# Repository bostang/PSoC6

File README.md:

# PSoC6
 Repository untuk program yang dijalankan pada PSoC6 (belajar dan hands-on project)

## Pranala Penting

[Hardware Abstraction Layer (HAL)](https://infineon.github.io/psoc6hal/html/index.html)

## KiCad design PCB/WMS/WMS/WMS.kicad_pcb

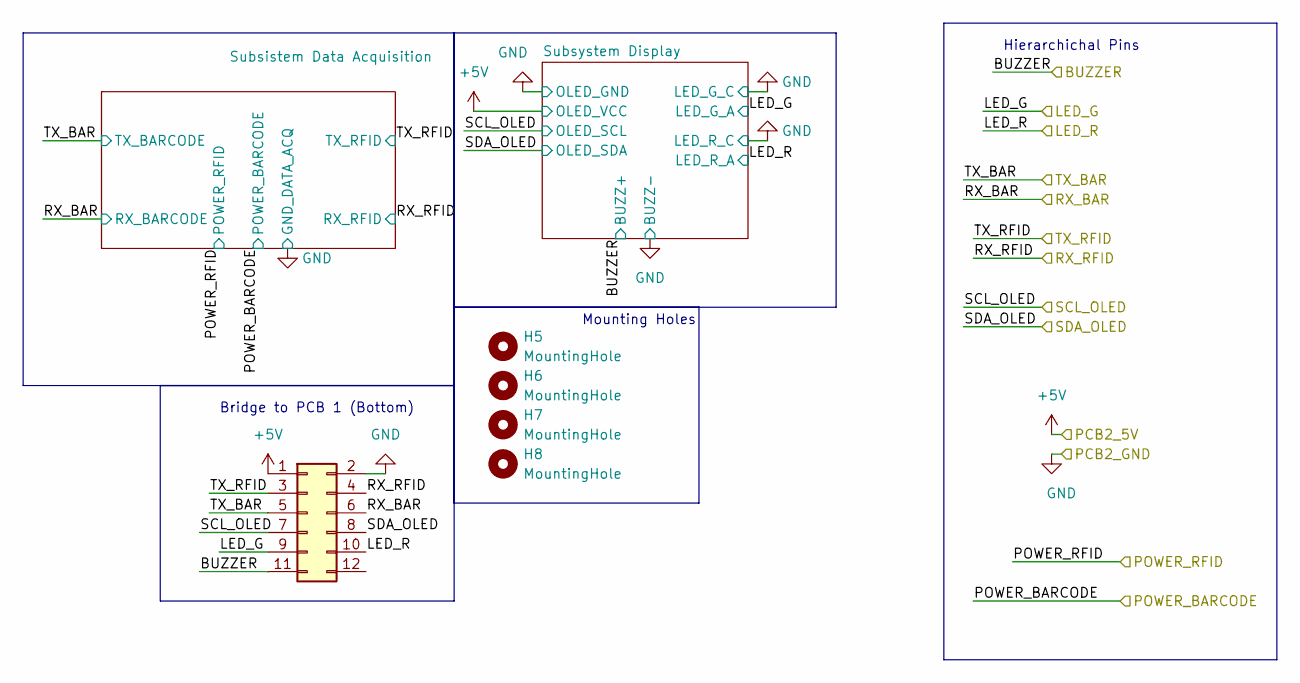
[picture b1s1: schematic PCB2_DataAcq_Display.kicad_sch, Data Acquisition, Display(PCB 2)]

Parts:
H5, H6, H7, H8: MountingHole; MountingHole_2.2mm_M2
J5: Conn_02x06_Odd_Even; JST_PHD_B12B-PHDSS_2x06_P2.00mm_Vertical

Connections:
+5V: J5.1; also elsewhere on the board
GND: J5.2; also elsewhere on the board
P6_0: J5.7; also elsewhere on the board
P6_1: J5.8; also elsewhere on the board
P9_0: J5.6; also elsewhere on the board
P9_1: J5.5; also elsewhere on the board
P9_2: J5.9; also elsewhere on the board
P9_4: J5.10; also elsewhere on the board
P12_0: J5.3; also elsewhere on the board
P12_1: J5.4; also elsewhere on the board
P12_3: J5.11; also elsewhere on the board

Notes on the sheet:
Mounting Holes
Bridge to PCB 1 (Bottom)
Hierarchichal Pins

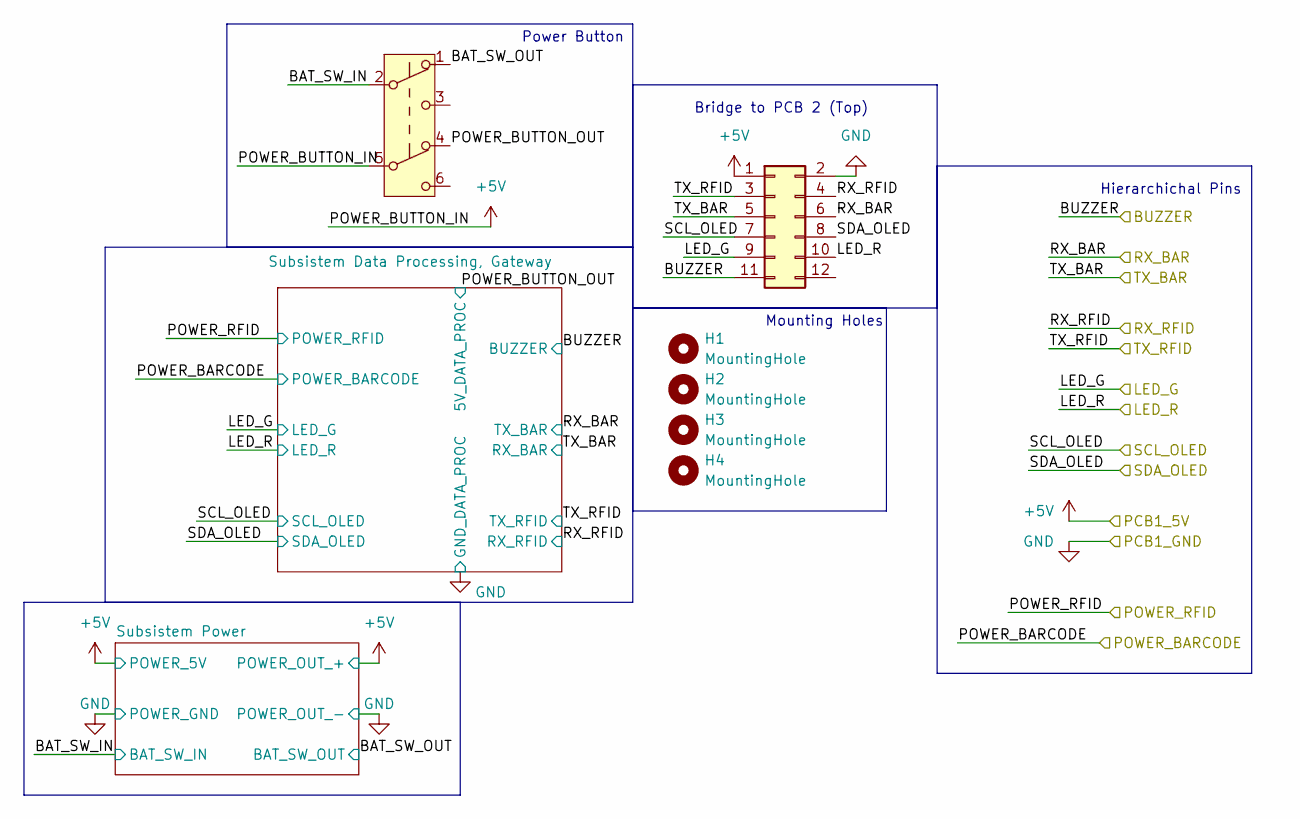
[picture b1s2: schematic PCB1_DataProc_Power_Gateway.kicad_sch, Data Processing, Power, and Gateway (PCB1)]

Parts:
H1, H2, H3, H4: MountingHole; MountingHole_2.2mm_M2
J4: Conn_02x06_Odd_Even; JST_PHD_B12B-PHDSS_2x06_P2.00mm_Vertical
SW2: SW_Push_DPDT; SW_E-Switch_EG2219_DPDT_Angled

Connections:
+5V: J4.1, SW2.5 (B); also elsewhere on the board
/PCB1 : Subsistem Data Processing, Gateway, Power/BAT_SW_IN: SW2.2 (B); also elsewhere on the board
/PCB1 : Subsistem Data Processing, Gateway, Power/BAT_SW_OUT: SW2.1 (A); also elsewhere on the board
/PCB1 : Subsistem Data Processing, Gateway, Power/POWER_BUTTON_OUT: SW2.4 (A); also elsewhere on the board
GND: J4.2; also elsewhere on the board
P6_0: J4.7; also elsewhere on the board
P6_1: J4.8; also elsewhere on the board
P9_0: J4.5; also elsewhere on the board
P9_1: J4.6; also elsewhere on the board
P9_2: J4.9; also elsewhere on the board
P9_4: J4.10; also elsewhere on the board
P12_0: J4.4; also elsewhere on the board
P12_1: J4.3; also elsewhere on the board
P12_3: J4.11; also elsewhere on the board

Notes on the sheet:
Hierarchichal Pins
Bridge to PCB 2 (Top)
Mounting Holes
Power Button

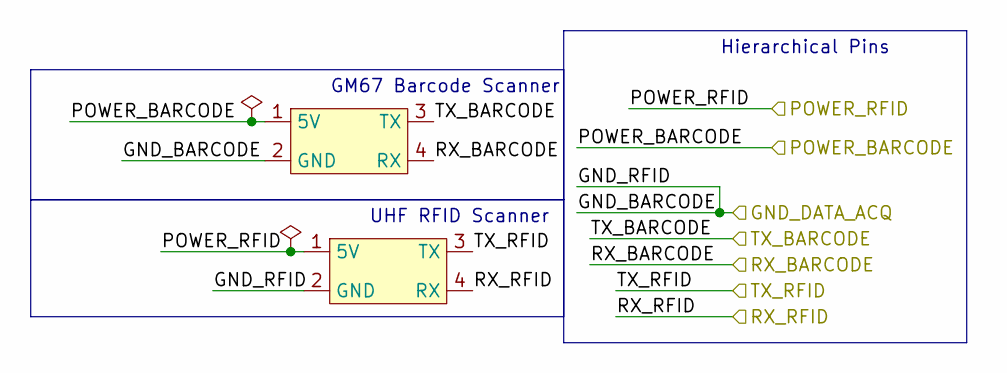
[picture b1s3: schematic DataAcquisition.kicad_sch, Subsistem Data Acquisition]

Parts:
U4, U5: GM67_Barcode_Scanner

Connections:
/PCB1 : Subsistem Data Processing, Gateway, Power/POWER_BARCODE: U4.1 (5V); also elsewhere on the board
/PCB1 : Subsistem Data Processing, Gateway, Power/POWER_RFID: U5.1 (5V); also elsewhere on the board
GND: U4.2 (GND), U5.2 (GND); also elsewhere on the board
P9_0: U4.4 (RX); also elsewhere on the board
P9_1: U4.3 (TX); also elsewhere on the board
P12_0: U5.3 (TX); also elsewhere on the board
P12_1: U5.4 (RX); also elsewhere on the board

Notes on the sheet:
UHF RFID Scanner
Hierarchical Pins
GM67 Barcode Scanner

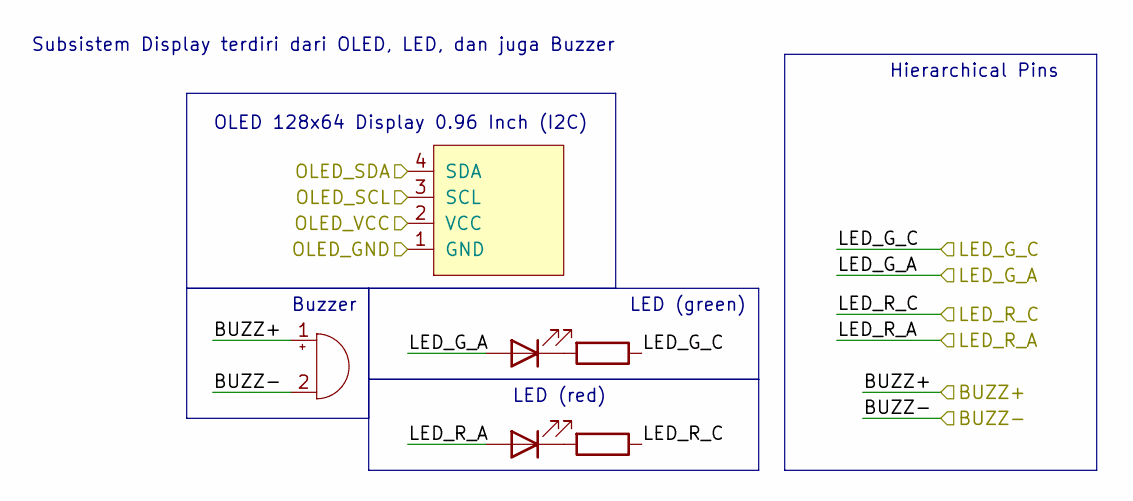
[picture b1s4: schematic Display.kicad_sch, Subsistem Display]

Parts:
BZ1: Buzzer; Buzzer_12x9.5RM7.6
Brd1: SSD1306; 128x64OLED
D1, D2: LED; LED_0805_2012Metric
R1, R2: R; R_0805_2012Metric

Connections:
+5V: Brd1.2 (VCC); also elsewhere on the board
GND: BZ1.2 (-), Brd1.1 (GND), R1.1, R2.1; also elsewhere on the board
unnamed: D1.1 (K), R1.2
unnamed: D2.1 (K), R2.2
P6_0: Brd1.3 (SCL); also elsewhere on the board
P6_1: Brd1.4 (SDA); also elsewhere on the board
P9_2: D1.2 (A); also elsewhere on the board
P9_4: D2.2 (A); also elsewhere on the board
P12_3: BZ1.1 (+); also elsewhere on the board

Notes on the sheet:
Subsistem Display terdiri dari OLED, LED, dan juga Buzzer
LED (red)
Buzzer
OLED 128x64 Display 0.96 Inch (I2C)
Hierarchical Pins
LED (green)

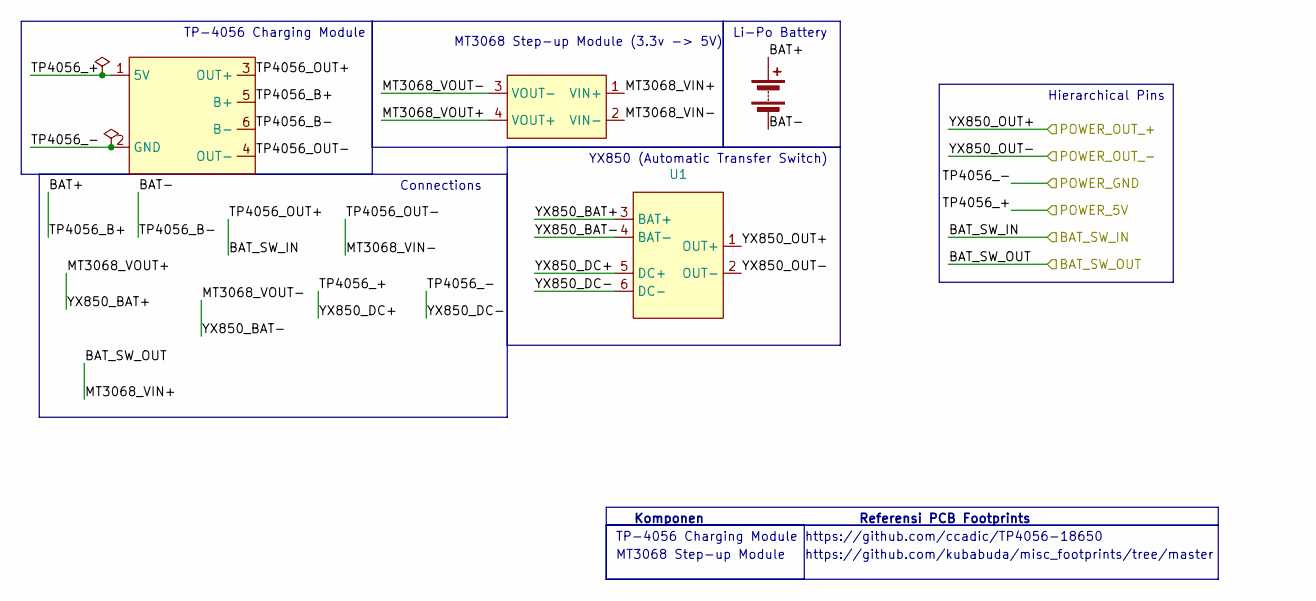
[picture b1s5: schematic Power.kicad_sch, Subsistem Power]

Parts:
BT1: Battery; JST_XH_B2B-XH-A_1x02_P2.50mm_Vertical
U1: YX850
U2: MT3608_module
U3: TP4056-18650

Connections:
+5V: U1.1 (OUT+), U1.5 (DC+), U3.1 (5V); also elsewhere on the board
/PCB1 : Subsistem Data Processing, Gateway, Power/BAT_SW_IN: U3.3 (OUT+); also elsewhere on the board
/PCB1 : Subsistem Data Processing, Gateway, Power/BAT_SW_OUT: U2.1 (VIN+); also elsewhere on the board
/PCB1 : Subsistem Data Processing, Gateway, Power/Subsistem Power/BAT+: BT1.1 (+), U3.5 (B+)
/PCB1 : Subsistem Data Processing, Gateway, Power/Subsistem Power/BAT-: BT1.2 (-), U3.6 (B-)
/PCB1 : Subsistem Data Processing, Gateway, Power/Subsistem Power/MT3068_VIN-: U2.2 (VIN-), U3.4 (OUT-)
/PCB1 : Subsistem Data Processing, Gateway, Power/Subsistem Power/MT3068_VOUT+: U1.3 (BAT+), U2.4 (VOUT+)
/PCB1 : Subsistem Data Processing, Gateway, Power/Subsistem Power/MT3068_VOUT-: U1.4 (BAT-), U2.3 (VOUT-)
GND: U1.2 (OUT-), U1.6 (DC-), U3.2 (GND); also elsewhere on the board

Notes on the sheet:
https://github.com/ccadic/TP4056-18650
https://github.com/kubabuda/misc_footprints/tree/master
TP-4056 Charging Module
Hierarchical Pins
Li-Po Battery
Komponen
MT3068 Step-up Module
YX850 (Automatic Transfer Switch)
Connections
Referensi PCB Footprints
MT3068 Step-up Module (3.3v -> 5V)

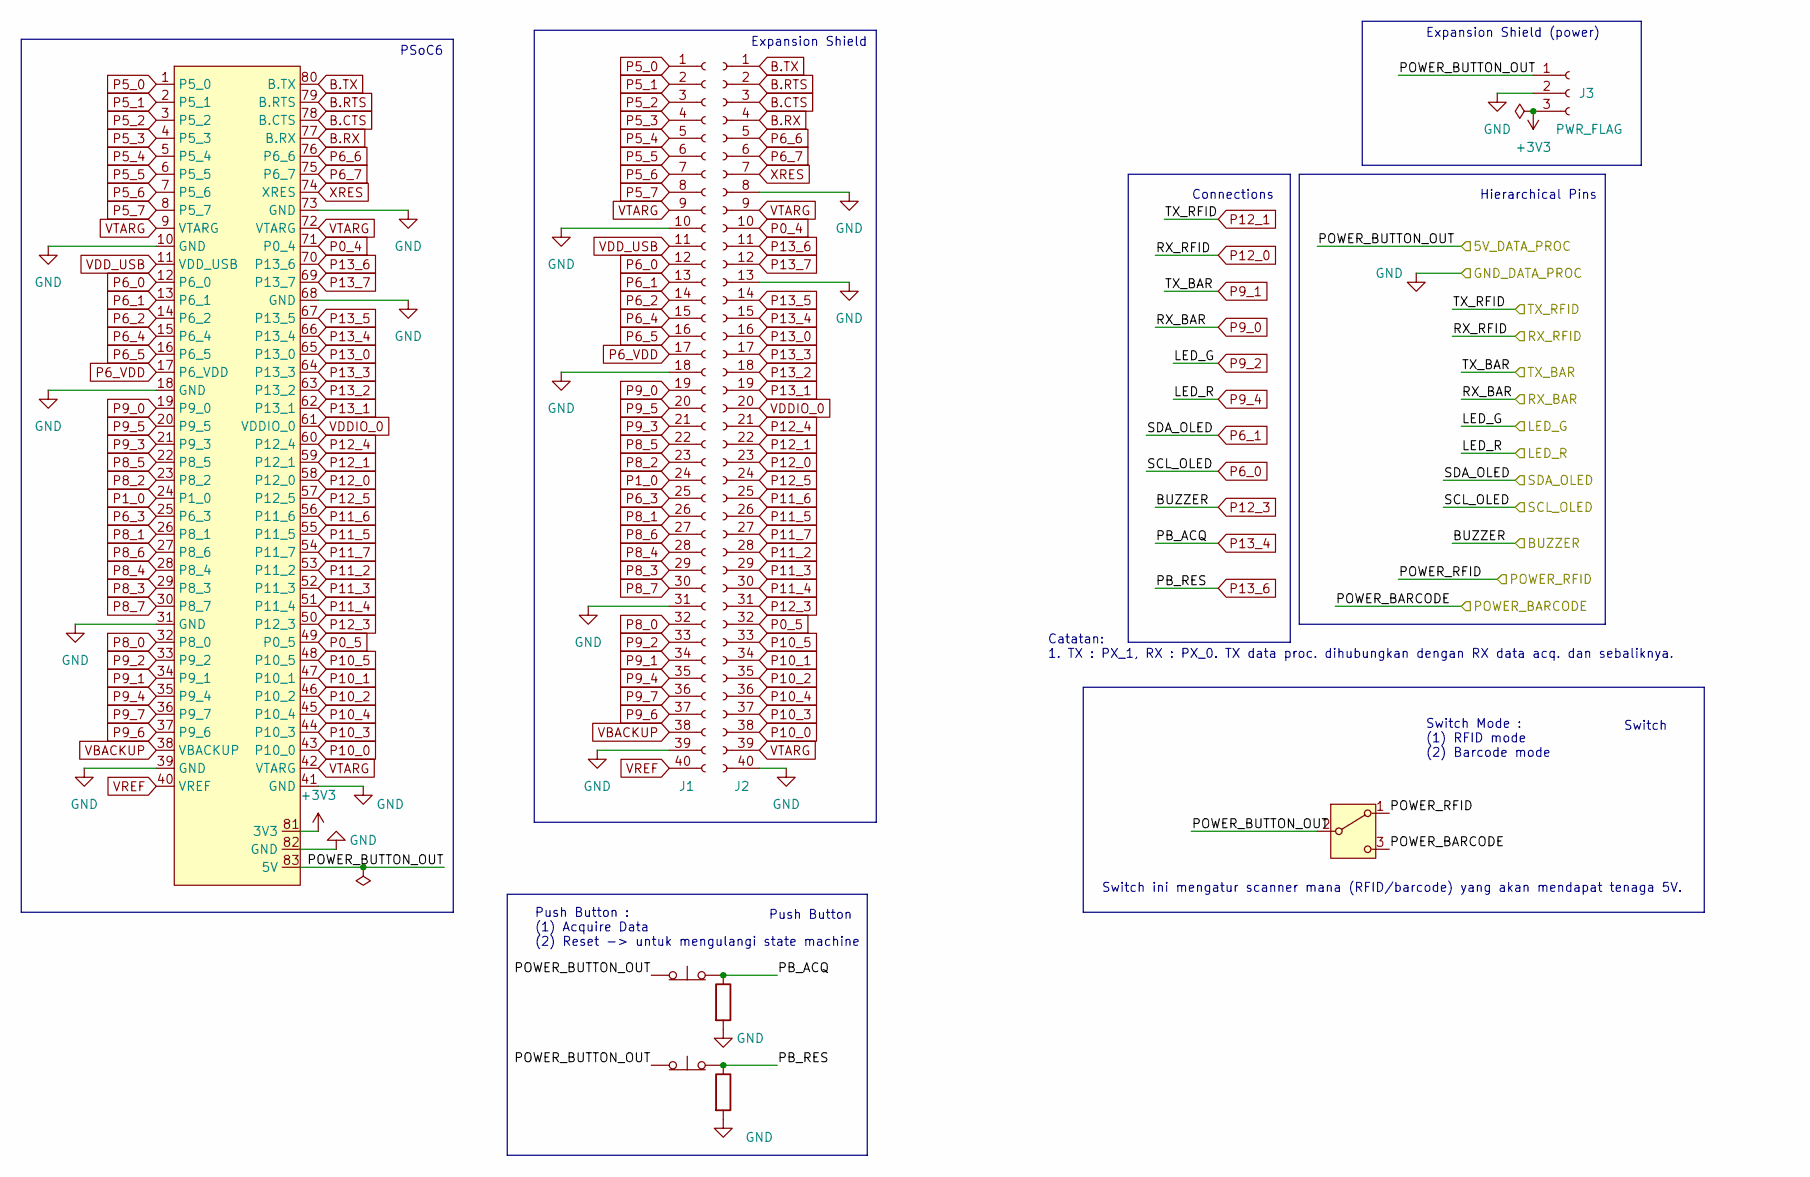
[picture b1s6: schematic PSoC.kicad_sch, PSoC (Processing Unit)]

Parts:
J1, J2: Conn_01x40_Socket; PinHeader_1x40_P2.54mm_Vertical
J3: Conn_01x03_Socket; PinHeader_1x03_P2.54mm_Vertical
R3, R4: R; R_0805_2012Metric
SW1, SW3: SW_Push_Open; SW_PUSH_6mm_H9.5mm
SW4: SW_SPDT; SW_E-Switch_EG1224_SPDT_Angled
U6: CY8CPROTO-062-4343W

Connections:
+3V3: J3.3, U6.81 (3V3)
/PCB1 : Subsistem Data Processing, Gateway, Power/POWER_BARCODE: SW4.3 (C); also elsewhere on the board
/PCB1 : Subsistem Data Processing, Gateway, Power/POWER_BUTTON_OUT: J3.1, SW1.1 (A), SW3.1 (A), SW4.2 (B), U6.83 (5V); also elsewhere on the board
/PCB1 : Subsistem Data Processing, Gateway, Power/POWER_RFID: SW4.1 (A); also elsewhere on the board
B.CTS: J2.3, U6.78 (B.CTS)
B.RTS: J2.2, U6.79 (B.RTS)
B.RX: J2.4, U6.77 (B.RX)
B.TX: J2.1, U6.80 (B.TX)
GND: J1.10, J1.18, J1.31, J1.39, J2.8, J2.13, J2.40, J3.2, R3.2, R4.2, U6.10 (GND), U6.18 (GND), U6.31 (GND), U6.39 (GND), U6.41 (GND), U6.68 (GND), U6.73 (GND), U6.82 (GND); also elsewhere on the board
P0_4: J2.10, U6.71 (P0_4)
P0_5: J2.32, U6.49 (P0_5)
P1_0: J1.24, U6.24 (P1_0)
P5_0: J1.1, U6.1 (P5_0)
P5_1: J1.2, U6.2 (P5_1)
P5_2: J1.3, U6.3 (P5_2)
P5_3: J1.4, U6.4 (P5_3)
P5_4: J1.5, U6.5 (P5_4)
P5_5: J1.6, U6.6 (P5_5)
P5_6: J1.7, U6.7 (P5_6)
P5_7: J1.8, U6.8 (P5_7)
P6_0: J1.12, U6.12 (P6_0); also elsewhere on the board
P6_1: J1.13, U6.13 (P6_1); also elsewhere on the board
P6_2: J1.14, U6.14 (P6_2)
P6_3: J1.25, U6.25 (P6_3)
P6_4: J1.15, U6.15 (P6_4)
P6_5: J1.16, U6.16 (P6_5)
P6_6: J2.5, U6.76 (P6_6)
P6_7: J2.6, U6.75 (P6_7)
P6_VDD: J1.17, U6.17 (P6_VDD)
P8_0: J1.32, U6.32 (P8_0)
P8_1: J1.26, U6.26 (P8_1)
P8_2: J1.23, U6.23 (P8_2)
P8_3: J1.29, U6.29 (P8_3)
P8_4: J1.28, U6.28 (P8_4)
P8_5: J1.22, U6.22 (P8_5)
P8_6: J1.27, U6.27 (P8_6)
P8_7: J1.30, U6.30 (P8_7)
P9_0: J1.19, U6.19 (P9_0); also elsewhere on the board
P9_1: J1.34, U6.34 (P9_1); also elsewhere on the board
P9_2: J1.33, U6.33 (P9_2); also elsewhere on the board
P9_3: J1.21, U6.21 (P9_3)
P9_4: J1.35, U6.35 (P9_4); also elsewhere on the board
P9_5: J1.20, U6.20 (P9_5)
P9_6: J1.37, U6.37 (P9_6)
P9_7: J1.36, U6.36 (P9_7)
P10_0: J2.38, U6.43 (P10_0)
P10_1: J2.34, U6.47 (P10_1)
P10_2: J2.35, U6.46 (P10_2)
P10_3: J2.37, U6.44 (P10_3)
P10_4: J2.36, U6.45 (P10_4)
P10_5: J2.33, U6.48 (P10_5)
P11_2: J2.28, U6.53 (P11_2)
P11_3: J2.29, U6.52 (P11_3)
P11_4: J2.30, U6.51 (P11_4)
P11_5: J2.26, U6.55 (P11_5)
P11_6: J2.25, U6.56 (P11_6)
P11_7: J2.27, U6.54 (P11_7)
P12_0: J2.23, U6.58 (P12_0); also elsewhere on the board
P12_1: J2.22, U6.59 (P12_1); also elsewhere on the board
P12_3: J2.31, U6.50 (P12_3); also elsewhere on the board
P12_4: J2.21, U6.60 (P12_4)
P12_5: J2.24, U6.57 (P12_5)
P13_0: J2.16, U6.65 (P13_0)
P13_1: J2.19, U6.62 (P13_1)
P13_2: J2.18, U6.63 (P13_2)
P13_3: J2.17, U6.64 (P13_3)
P13_4: J2.15, R3.1, SW1.2 (B), U6.66 (P13_4)
P13_5: J2.14, U6.67 (P13_5)
P13_6: J2.11, R4.1, SW3.2 (B), U6.70 (P13_6)
P13_7: J2.12, U6.69 (P13_7)
VBACKUP: J1.38, U6.38 (VBACKUP)
VDDIO_0: J2.20, U6.61 (VDDIO_0)
VDD_USB: J1.11, U6.11 (VDD_USB)
VREF: J1.40, U6.40 (VREF)
VTARG: J1.9, J2.9, J2.39, U6.9 (VTARG), U6.42 (VTARG), U6.72 (VTARG)
XRES: J2.7, U6.74 (XRES)

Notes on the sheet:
PSoC6
Expansion Shield (power)
Push Button : (1) Acquire Data (2) Reset -> untuk mengulangi state machine
Switch
Connections
Expansion Shield
Hierarchical Pins
Switch ini mengatur scanner mana (RFID/barcode) yang akan mendapat tenaga 5V.
Catatan: 1. TX : PX_1, RX : PX_0. TX data proc. dihubungkan dengan RX data acq. dan sebaliknya.
Switch Mode : (1) RFID mode (2) Barcode mode
Push Button

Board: 2 copper layers, 32 parts (5 on the bottom side), 86 nets, no tracks yet.

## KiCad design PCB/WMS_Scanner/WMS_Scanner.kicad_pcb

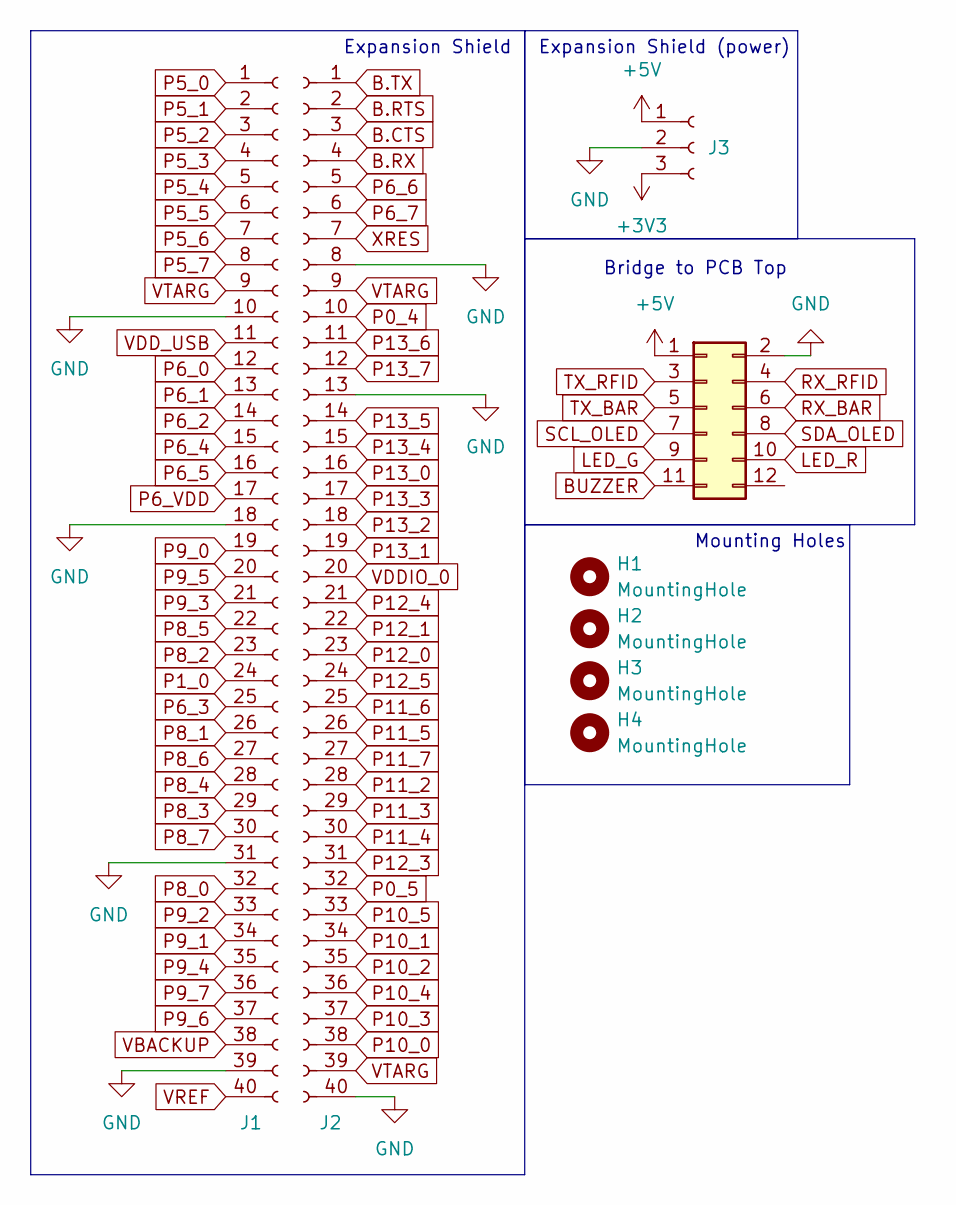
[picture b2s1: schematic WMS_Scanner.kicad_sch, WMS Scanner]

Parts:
H1, H2, H3, H4: MountingHole; MountingHole_2.2mm_M2
J1, J2: Conn_01x40_Socket; PinHeader_1x40_P2.54mm_Vertical
J3: Conn_01x03_Socket; PinHeader_1x03_P2.54mm_Vertical
J4: Conn_02x06_Odd_Even; JST_PHD_B12B-PHDSS_2x06_P2.00mm_Vertical

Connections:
+3V3: J3.3
+5V: J3.1, J4.1
B.CTS: J2.3
B.RTS: J2.2
B.RX: J2.4
B.TX: J2.1
BUZZER: J4.11
GND: J1.10, J1.18, J1.31, J1.39, J2.8, J2.13, J2.40, J3.2, J4.2
LED_G: J4.9
LED_R: J4.10
P0_4: J2.10
P0_5: J2.32
P1_0: J1.24
P5_0: J1.1
P5_1: J1.2
P5_2: J1.3
P5_3: J1.4
P5_4: J1.5
P5_5: J1.6
P5_6: J1.7
P5_7: J1.8
P6_0: J1.12
P6_1: J1.13
P6_2: J1.14
P6_3: J1.25
P6_4: J1.15
P6_5: J1.16
P6_6: J2.5
P6_7: J2.6
P6_VDD: J1.17
P8_0: J1.32
P8_1: J1.26
P8_2: J1.23
P8_3: J1.29
P8_4: J1.28
P8_5: J1.22
P8_6: J1.27
P8_7: J1.30
P9_0: J1.19
P9_1: J1.34
P9_2: J1.33
P9_3: J1.21
P9_4: J1.35
P9_5: J1.20
P9_6: J1.37
P9_7: J1.36
P10_0: J2.38
P10_1: J2.34
P10_2: J2.35
P10_3: J2.37
P10_4: J2.36
P10_5: J2.33
P11_2: J2.28
P11_3: J2.29
P11_4: J2.30
P11_5: J2.26
P11_6: J2.25
P11_7: J2.27
P12_0: J2.23
P12_1: J2.22
P12_3: J2.31
P12_4: J2.21
P12_5: J2.24
P13_0: J2.16
P13_1: J2.19
P13_2: J2.18
P13_3: J2.17
P13_4: J2.15
P13_5: J2.14
P13_6: J2.11
P13_7: J2.12
RX_BAR: J4.6
RX_RFID: J4.4
SCL_OLED: J4.7
SDA_OLED: J4.8
TX_BAR: J4.5
TX_RFID: J4.3
VBACKUP: J1.38
VDDIO_0: J2.20
VDD_USB: J1.11
VREF: J1.40
VTARG: J1.9, J2.9, J2.39
XRES: J2.7

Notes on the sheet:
Bridge to PCB Top
Expansion Shield
Mounting Holes
Expansion Shield (power)

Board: 2 copper layers, 8 parts (0 on the bottom side), 3 nets, no tracks yet.

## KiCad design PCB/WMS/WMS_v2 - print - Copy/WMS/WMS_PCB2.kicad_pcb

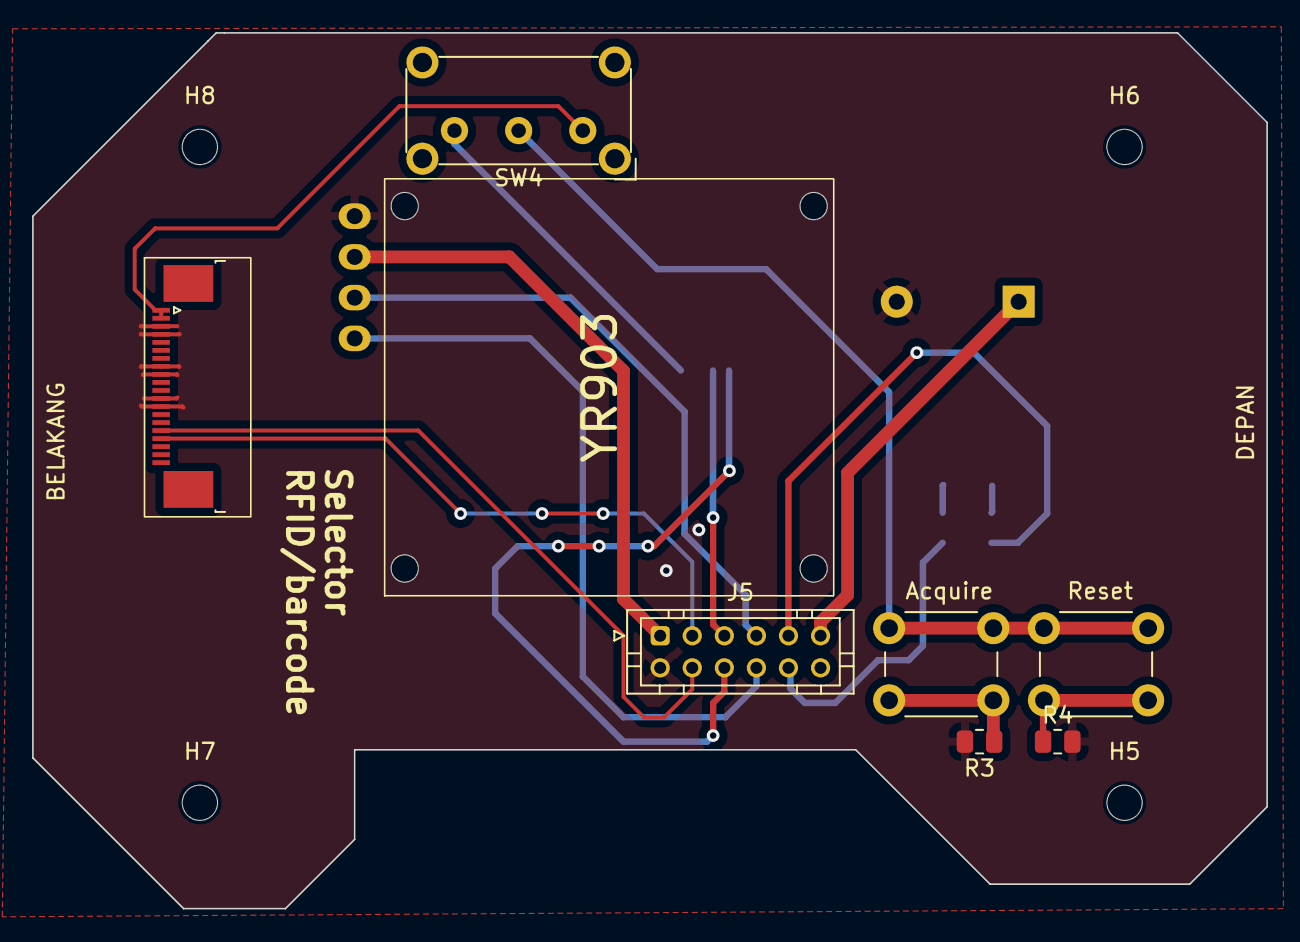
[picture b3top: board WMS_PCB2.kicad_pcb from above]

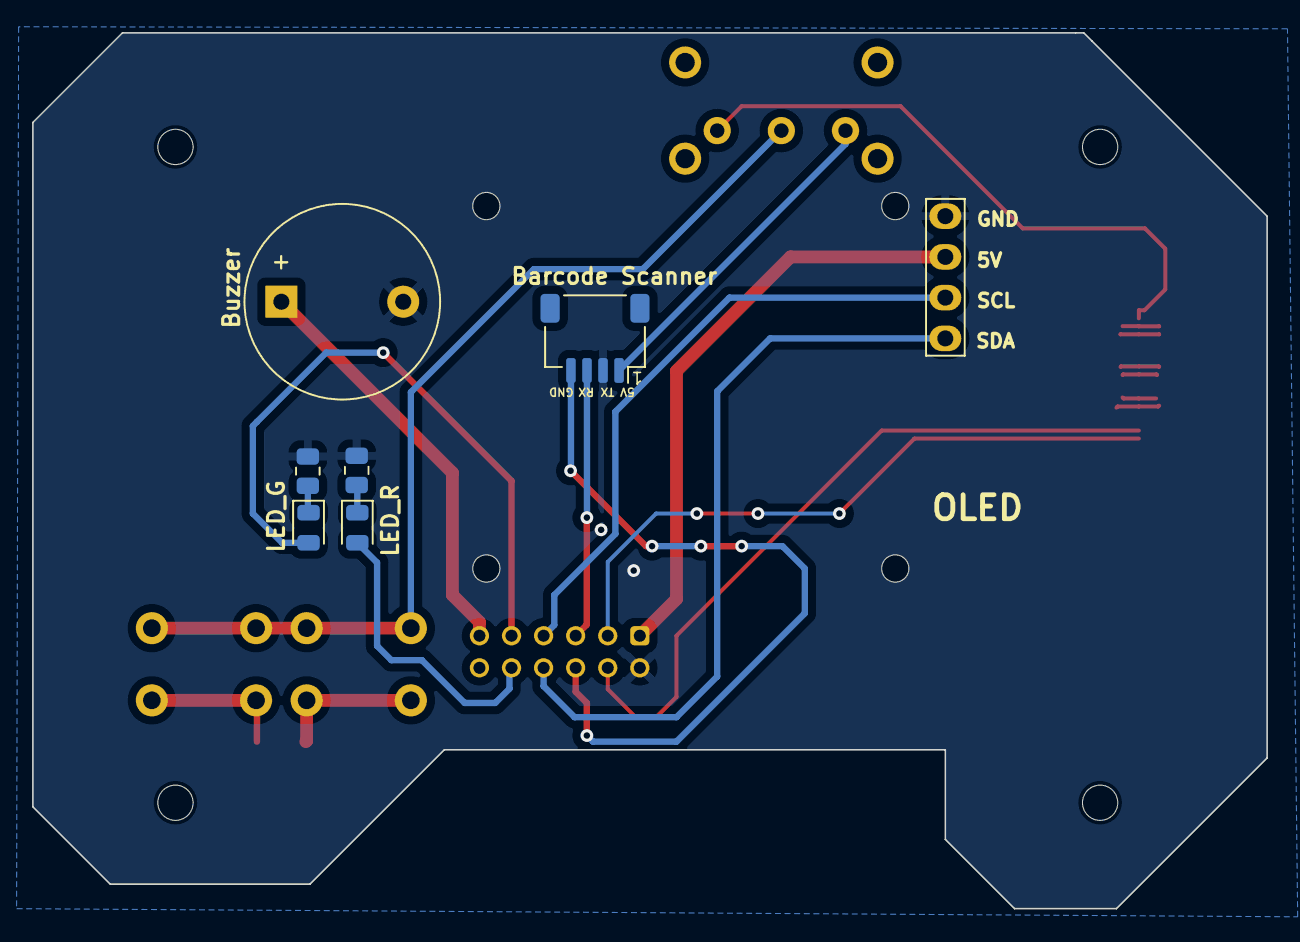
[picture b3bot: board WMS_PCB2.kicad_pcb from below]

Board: 2 copper layers, 77.0 x 54.6 mm, 18 parts (7 on the bottom side), 18 nets.

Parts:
BZ1: Buzzer; Buzzer_12x9.5RM7.6
Brd1: SSD1306; 128x64OLED_v2
D1, D2: LED; LED_0805_2012Metric
H5, H6, H7, H8: MountingHole; MountingHole_2.2mm_M2
J5: Conn_02x06_Odd_Even; JST_PHD_B12B-PHDSS_2x06_P2.00mm_Vertical
R1, R2, R3, R4: R; R_0805_2012Metric
SW1, SW3: SW_Push_Open; SW_PUSH_6mm_H9.5mm
SW4: SW_SPDT; SW_E-Switch_EG1224_SPDT_Angled
U4: GM67_Barcode_Scanner
U7: YR903_RFID_Scanner_FPC

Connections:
+5V: Brd1.2 (VCC), J5.1
/PCB1 : Subsistem Data Processing, Gateway, Power/POWER_BARCODE: SW4.3 (C), U4.1 (5V)
/PCB1 : Subsistem Data Processing, Gateway, Power/POWER_BUTTON_OUT: SW1.1 (A), SW3.1 (A), SW4.2 (B)
/PCB1 : Subsistem Data Processing, Gateway, Power/POWER_RFID: SW4.1 (A), U7.1 (VCC), U7.2 (VCC)
GND: BZ1.2 (-), Brd1.1 (GND), J5.2, R1.1, R2.1, R3.2, R4.2, U4.2 (GND), U7.3 (GND), U7.4 (GND), U7.8 (GND), U7.9 (GND), U7.12 (GND), U7.13 (GND)
unnamed: D1.1 (K), R1.2
unnamed: D2.1 (K), R2.2
P6_0: Brd1.3 (SCL), J5.7
P6_1: Brd1.4 (SDA), J5.8
P9_0: J5.6, U4.4 (RX)
P9_1: J5.5, U4.3 (TX)
P9_2: D1.2 (A), J5.9
P9_4: D2.2 (A), J5.10
P12_0: J5.3, U7.17 (TXD)
P12_1: J5.4, U7.16 (RXD)
P12_3: BZ1.1 (+), J5.11
P13_4: R3.1, SW1.2 (B)
P13_6: R4.1, SW3.2 (B)

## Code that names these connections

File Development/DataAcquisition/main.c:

// Program DataAcquisition
	// Realisasi modul data acquisition pada subsistem data acquisition&processing warehouse management system
	// Yang menerima input data berupa tag RFID atau tag barcode
// KAMUS
	// Konstanta
		//
	// Fungsi / Prosedur
		// procedure handle_error
			// error handling function
	// Variabel
		//
// PINOUT
	// PSoC			<->		RFID Interface
		// ... [belum]
	// PSoC			<->		Barcode Scanner
		//	P9_1 (tx)	<->		Rx
		// 	P9_0 (rx)	<->		Tx
		//	5V			<->		5V
		//	GND			<->		GND

// Programmer : Bostang 

// ALGORITMA UTAMA

// INCLUDE LIBRARY
#include "cyhal.h"
#include "cybsp.h"
#include "cy_retarget_io.h"

// DEKLARASI KONSTANTA
//#define pin_barcode_tx P9_1
//#define pin_barcode_rx P9_0
#define pin_barcode_tx P12_1
#define pin_barcode_rx P12_0
/*******************************************************************************
* Function Name: handle_error
********************************************************************************
* Summary:
* User defined error handling function.
*
* Parameters:
*  void
*
* Return:
*  void
*
*******************************************************************************/
void handle_error(void)
{
     /* Disable all interrupts. */
    __disable_irq();

    CY_ASSERT(0);
}

/*******************************************************************************
* Function Name: main
********************************************************************************
* Summary:
* This is the main function.
* Reads one byte from the serial terminal and echoes back the read byte.
*
* Parameters:
*  void
*
* Return:
*  int
*
*******************************************************************************/
int main(void)
{
    cy_rslt_t result;
    #if defined(CY_DEVICE_SECURE)
        cyhal_wdt_t wdt_obj;
        /* Clear watchdog timer so that it doesn't trigger a reset */
        result = cyhal_wdt_init(&wdt_obj, cyhal_wdt_get_max_timeout_ms());
        CY_ASSERT(CY_RSLT_SUCCESS == result);
        cyhal_wdt_free(&wdt_obj);
    #endif

    uint8_t read_data; /* Variable to store the received character
                        * through terminal */

    /* Initialize the device and board peripherals */
    result = cybsp_init();
    if (result != CY_RSLT_SUCCESS)
    {
        handle_error();
    }

    /* Initialize retarget-io to use the debug UART port */
#ifdef XMC72_EVK
    result = cy_retarget_io_init(CYBSP_DEBUG_UART_TX, CYBSP_DEBUG_UART_RX,
                                 CY_RETARGET_IO_BAUDRATE);

    if (result != CY_RSLT_SUCCESS)
    {
        handle_error();
    }
#else
    cyhal_uart_t uart_obj;
    cyhal_uart_t uart_obj_barcode;
	#define TX_BUF_SIZE     4
    size_t tx_length = TX_BUF_SIZE;

   // ketika ini diaktifkan, maka kita bisa mengirim ke terminal dengan 'printf', tetapi akan konflik dengan cyhal_uart_init
//    result = cy_retarget_io_init_fc(CYBSP_DEBUG_UART_TX,
//    								CYBSP_DEBUG_UART_RX,
//                                    CYBSP_DEBUG_UART_CTS,
//                                    CYBSP_DEBUG_UART_RTS,
//                                    CY_RETARGET_IO_BAUDRATE);


    /* Initialize the UART configuration structure */
//    const cyhal_uart_cfg_t uart_config =
//    {
//        .data_bits = DATA_BITS_8,
//        .stop_bits = STOP_BITS_1,
//        .parity = CYHAL_UART_PARITY_NONE,
//        .rx_buffer = rx_buf,
//        .rx_buffer_size = RX_BUF_SIZE
//    };

    // mendeklarasikan uart object untuk USB-TTL (simulasi receiver)
    result = cyhal_uart_init(&uart_obj, CYBSP_DEBUG_UART_TX, CYBSP_DEBUG_UART_RX,NC,NC, NULL, NULL);
    if (result != CY_RSLT_SUCCESS)
    {
        handle_error();
    }


    // mendeklarasikan uart object untuk barcode reader (sender)
    result = cyhal_uart_init(&uart_obj_barcode, pin_barcode_tx, pin_barcode_rx,NC,NC, NULL, NULL);
    if (result != CY_RSLT_SUCCESS)
    {
        handle_error();
    }
#endif
    /* \x1b[2J\x1b[;H - ANSI ESC sequence for clear screen */
//    printf("\x1b[2J\x1b[;H");

    // printf() menjadi tidak bisa dipakai karena retarget_io_init tidak dipakai
//    printf("***********************************************************\r\n");
//    printf("HAL: UART Transmit and Receive\r\n");
//    printf("***********************************************************\r\n\n");
//    printf(">> Start typing to see the echo on the screen \r\n\n");

    uint8_t tx_buf[TX_BUF_SIZE] = {'1','2','3','4'};
    char msg1[15] = "----------";
    size_t len_msg1 = sizeof(msg1);

    cyhal_uart_write(&uart_obj,(void*) tx_buf,&tx_length);
    cyhal_uart_putc(&uart_obj,'\n');
    cyhal_uart_write(&uart_obj,(void*) msg1,&len_msg1);
    cyhal_uart_putc(&uart_obj,'\n');

    __enable_irq();
 
    for (;;)
    {
        if (CY_RSLT_SUCCESS == cyhal_uart_getc(&uart_obj_barcode,
                                               &read_data, 0))
        {
            if (CY_RSLT_SUCCESS != cyhal_uart_putc(&uart_obj,
                                                   read_data))
            {
                handle_error();
            }
        }
        else
        {
            handle_error();
        }
    }
}

/* [] END OF FILE */

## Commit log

2023-12-02 + Training repos
    Menambahkan repo pelatihan pemrograman PSoC dari github repo resmi Infineon
2023-12-02 + Documents + Pranala
    Menambahkan pranala yang penting untuk projek dan juga dokumen-dokumen yang diperlukan
2023-12-03 + GPIO project
    mampu mengendalikan pushbutton dan LED (GPIO) dengan mengikuti example code GPIO
2023-12-06 +TestUART
    Kode untuk mengetes Barcode scanner pada Arduino UNO
2023-12-06 +test RFID
    kode untuk menggunakan RFID pada ESP32 dan menampilkannya pada Serial monitor
2023-12-09 Update 1.md
    + cara build kode yang cepat
    + workflow pengembangan kode PSoC
2023-12-09 +ReceiveUART
    Mengetikkan karakter pada keyboard lalu mengirimkan ke USB-TTL (dilihat di terminal baru)
2023-12-09 +TransmitnReceive
    Membuat dua objek UART. Mengirimkan data dari barcode scanner dan membaca pada USB-TTL
2023-12-10 Update 1.md
    +catatan tentang error handling
2023-12-10 +foto terminal_mtb
2023-12-10 Update 1.md
    + catatan seputar terminal mtb
2023-12-10 + Data Acquisition
    Memulai pengembangan modul data acquisition pada sistem warehouse management system
2023-12-11 +RFID_UART
    memulai projek membaca RFID (UART) dengan PSoC6
2023-12-11 + FeeRTOS Example
    menambahkan contoh membuat task dengan FreeRTOS untuk blinking LED
2023-12-11 +instruksi FreeRTOS
    menambahkan README.md pada contoh menggunakan freeRTOS
2023-12-11 Update main.c RFID_UART
2023-12-14 UART_arbitrary_pin
    Menggunakan UART di pin sembarang
2023-12-14 Create README.md
    POST to HTTP
2023-12-14 +DataAcquisition_and_Processing
2023-12-14 +file data acquisition and processing
2023-12-15 +Arduino_RFIDStartRead.ino
    Program untuk ESP32 yang dibuat di Arduino IDE untuk memverifikasi bahwa ketika perintah (bytes) start read dikirim, maka LED pada RFID interface menyala dan ketika perintah (bytes) stop read dikirim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
2023-12-16 +Cetak arrayByte ke Terminal
    - mencetak array byte ke terminal byte per byte menggunakan for loop.
    - menggunakan format specifier %02X
2023-12-16 Rename UART_arbitrary_pin to UART_arbitrary_pin.c
2023-12-16 +BUG_RFIDStartRead.c
    Menambahkan program (masih belum berhasil) untuk memulai mode baca pada RFID interface dengan PSoC
2023-12-16 Create Arduino_RFID_StartRead
    + versi tanpa guru meditation error
2023-12-16 Rename Arduino_RFID_StartRead to Arduino_RFID_StartRead_v2.ino
2023-12-16 Create Arduino_testLCD16x2.ino
    Pengujian LCD16x2 pada ESP32
2023-12-16 Create RFID_OLED.ino
    menggunakan RFID dengan OLED
2023-12-16 Create test_buzzer.ino
    Melakukan pengujian terhadap buzzer berbunyi
2023-12-17 Create TrynError
    data acq file
2023-12-17 VariableFromFunction
    memodifikasi array of uint8_t dengan menggunakan fungsi eksternal
2024-01-25 +menggunakan oled ssd1306
2024-01-25 +display graphics OLED
    menampilkan grafik menggunakan u8g2
2024-03-05 +PCB_v1
    menambahkan desain skematik PCB menggunakan kicad
2024-03-06 +Update PCB (v.1)
    membuat PCB versi 1
2024-03-13 + baca RFID module YR903 dengan esp32
2024-03-14 +YR903
    pengembangan YR903 (memulai)
2024-03-14 +baca data dari RFID ke PSoC
    membaca data dari RFID ke PSoC
2024-03-14 +YR903 rfid development
    pengembangan modul rfid scanner rfid yr903
2024-03-14 +RFID sampai array of strings
2024-03-15 + Program parsing SD card
    dari sebuah isi file csv berupa string panjang menjadi beberapa array of uint8_t yang siap dituliskan ke RFID tag
2024-03-26 +update PCBv2_print
    menambahkan file PCB v2 untuk dicetak
2024-04-19 +kode development integrasi
2024-04-24 +integrasi5,6 (gagal)
2024-04-24 +integrasi 4 (restore)
2024-04-24 fix integrasi 5 & 6
2024-04-24 + kode integrasi_6 : scan sampai tampil ke OLED
2024-04-25 +kode WMS v1
2024-05-08 Create http_client.c end-to-end barcode
2024-05-08 +WMS_v1.1
2024-05-08 +file WMS_v1.1
2024-05-08 +WMS1.1 zip
2024-05-09 +WMS_v2.0
2024-05-09 +konten WMSv2.0
2024-06-08 +WMS_v4_1
2024-06-14 +stable v1 code
    development WMS v4.6 -> stable v.1
2024-06-14 final version of PCB
2024-07-03 +full sourcecode (zipped)
